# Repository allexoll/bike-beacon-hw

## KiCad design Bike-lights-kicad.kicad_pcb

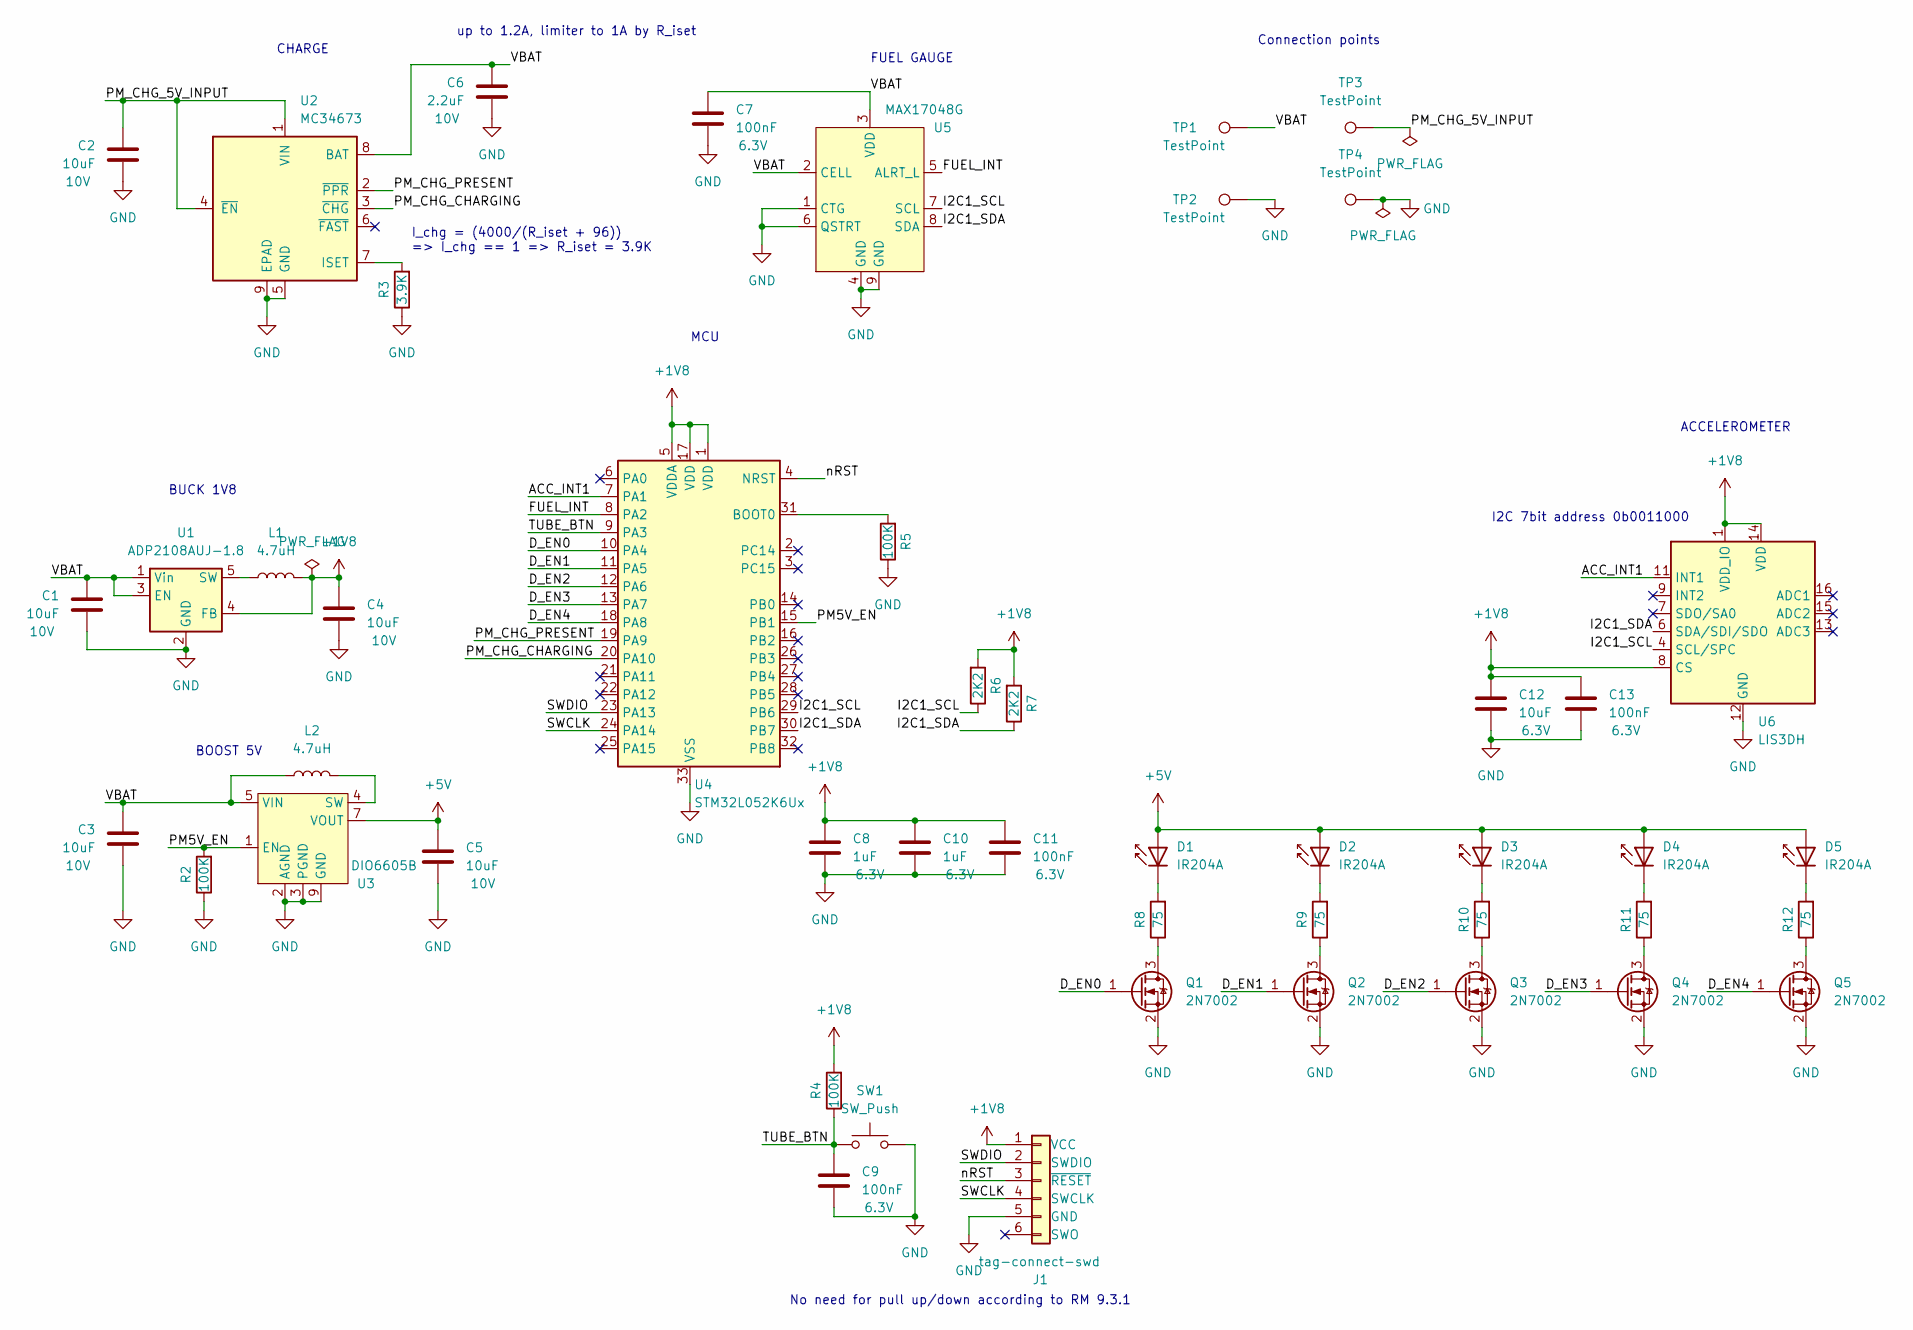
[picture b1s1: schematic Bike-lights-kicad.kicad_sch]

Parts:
C1, C2, C3, C4, C5: 10uF; C_0805_2012Metric; Rating 10V
C6: 2.2uF; C_0805_2012Metric; Rating 10V
C7, C9, C11, C13: 100nF; C_0603_1608Metric; Rating 6.3V
C8, C10: 1uF; C_0603_1608Metric; Rating 6.3V
C12: 10uF; C_0805_2012Metric; Rating 6.3V
D1, D2, D3, D4, D5: IR204A; LED_D3.0mm_IRBlack
J1: tag-connect-swd; Tag-Connect_TC2030-IDC-NL_2x03_P1.27mm_Vertical
L1, L2: 4.7uH; L_Taiyo-Yuden_NR-40xx; MPN NRS4012T4R7MDGJ
Q1, Q2, Q3, Q4, Q5: 2N7002; SOT-23
R2, R4, R5: 100K; R_0603_1608Metric
R3: 3.9K; R_0603_1608Metric
R6, R7: 2K2; R_0603_1608Metric
R8, R9, R10, R11, R12: 75; R_0603_1608Metric
SW1: SW_Push; SW_Push_1P1T_NO_CK_KSC6xxJ
TP1, TP2, TP3, TP4: TestPoint; TestPoint_Pad_4.0x4.0mm
U1: ADP2108AUJ-1.8; TSOT-23-5
U2: MC34673; DFN-8-1EP_3x2mm_P0.5mm_EP1.75x1.45mm
U3: DIO6605B; TDFN-8-1EP_3x2mm_P0.5mm_EP1.4x1.4mm
U4: STM32L052K6Ux; QFN-32-1EP_5x5mm_P0.5mm_EP3.45x3.45mm
U5: MAX17048G; WDFN-8-1EP_2x2mm_P0.5mm_EP0.8x1.2mm
U6: LIS3DH; LGA-16_3x3mm_P0.5mm_LayoutBorder3x5y

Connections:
+1V8: C4.1, C8.1, C10.1, C11.1, C12.1, C13.1, J1.1 (VCC), L1.2, R4.2, R6.2, R7.2, U1.4 (FB), U4.1 (VDD), U4.5 (VDDA), U4.17 (VDD), U6.1 (VDD_IO), U6.8 (CS), U6.14 (VDD)
+5V: C5.1, D1.2 (A), D2.2 (A), D3.2 (A), D4.2 (A), D5.2 (A), U3.7 (VOUT)
/ACC_INT1: U4.7 (PA1), U6.11 (INT1)
/D_EN0: Q1.1 (G), U4.10 (PA4)
/D_EN1: Q2.1 (G), U4.11 (PA5)
/D_EN2: Q3.1 (G), U4.12 (PA6)
/D_EN3: Q4.1 (G), U4.13 (PA7)
/D_EN4: Q5.1 (G), U4.18 (PA8)
/FUEL_INT: U4.8 (PA2), U5.5 (ALRT_L)
/I2C1_SCL: R6.1, U4.29 (PB6), U5.7 (SCL), U6.4 (SCL/SPC)
/I2C1_SDA: R7.1, U4.30 (PB7), U5.8 (SDA), U6.6 (SDA/SDI/SDO)
/PM5V_EN: R2.2, U3.1 (EN), U4.15 (PB1)
/PM_CHG_5V_INPUT: C2.1, TP3.1, U2.1 (VIN), U2.4 (~EN)
/PM_CHG_CHARGING: U2.3 (~CHG), U4.20 (PA10)
/PM_CHG_PRESENT: U2.2 (~PPR), U4.19 (PA9)
/SWCLK: J1.4 (SWCLK), U4.24 (PA14)
/SWDIO: J1.2 (SWDIO), U4.23 (PA13)
/TUBE_BTN: C9.1, R4.1, SW1.1, U4.9 (PA3)
/VBAT: C1.1, C3.1, C6.1, C7.1, L2.1, TP1.1, U1.1 (Vin), U1.3 (EN), U2.8 (BAT), U3.5 (VIN), U5.2 (CELL), U5.3 (VDD)
/nRST: J1.3 (~RESET), U4.4 (NRST)
GND: C1.2, C2.2, C3.2, C4.2, C5.2, C6.2, C7.2, C8.2, C9.2, C10.2, C11.2, C12.2, C13.2, J1.5 (GND), Q1.2 (S), Q2.2 (S), Q3.2 (S), Q4.2 (S), Q5.2 (S), R2.1, R3.1, R5.1, SW1.2, TP2.1, TP4.1, U1.2 (GND), U2.5 (GND), U2.9 (EPAD), U3.2 (AGND), U3.3 (PGND), U3.9 (GND), U4.33 (VSS), U5.1 (CTG), U5.4 (GND), U5.6 (QSTRT), U5.9 (GND), U6.5 (GND), U6.10 (GND), U6.12 (GND)
unnamed: D1.1 (K), R8.2
unnamed: D2.1 (K), R9.2
unnamed: D3.1 (K), R10.2
unnamed: D4.1 (K), R11.2
unnamed: D5.1 (K), R12.2
unnamed: L1.1, U1.5 (SW)
unnamed: L2.2, U3.4 (SW)
unnamed: Q1.3 (D), R8.1
unnamed: Q2.3 (D), R9.1
unnamed: Q3.3 (D), R10.1
unnamed: Q4.3 (D), R11.1
unnamed: Q5.3 (D), R12.1
unnamed: R3.2, U2.7 (ISET)
unnamed: R5.2, U4.31 (BOOT0)

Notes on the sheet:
CHARGE
BUCK 1V8
BOOST 5V
FUEL GAUGE
No need for pull up/down according to RM 9.3.1
up to 1.2A, limiter to 1A by R_iset
I_chg = (4000/(R_iset + 96)) => I_chg == 1 => R_iset = 3.9K
I2C 7bit address 0b0011000
Connection points
MCU
ACCELEROMETER

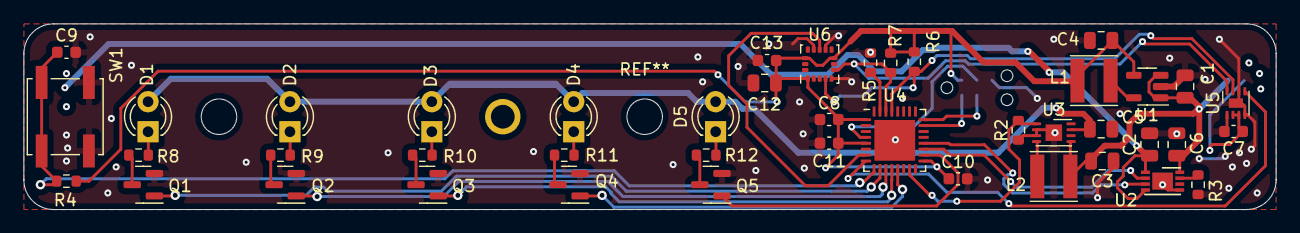
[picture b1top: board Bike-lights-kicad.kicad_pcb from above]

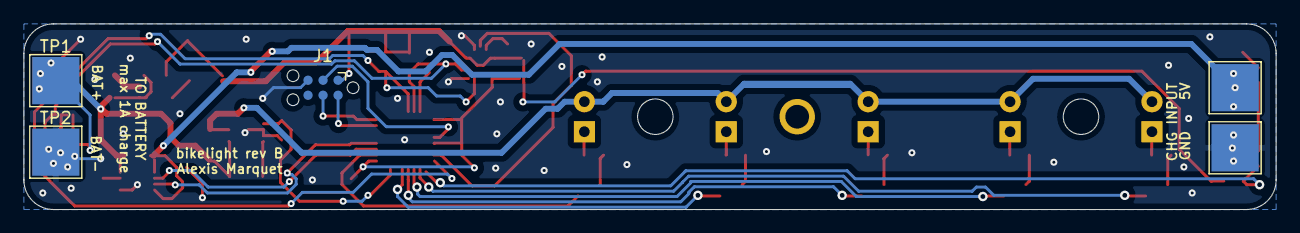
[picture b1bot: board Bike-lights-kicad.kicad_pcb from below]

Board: 2 copper layers, 105.9 x 15.7 mm, 48 parts (5 on the bottom side), 35 nets.

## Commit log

2022-09-22 remove backup, sync submodule and add ignore
2022-09-24 finished schematic and footprint assignment
2022-09-24 output ready
2022-09-26 add makefile for CI
2022-09-26 Update .gitlab-ci.yml file
2022-09-26 add kiplot prefs
2022-09-26 fix kiplot
2022-09-26 update kiplot
2022-09-26 fixed 3 unconnected nets after sending to production...
2022-09-26 fix submodules
2022-09-26 add sym table
2022-09-26 fix missing parenthesis
2022-09-26 filter warnigns
2022-09-26 fix bom
2022-09-26 fix gerber
2022-09-26 add technical layers
2022-09-26 fix layers
